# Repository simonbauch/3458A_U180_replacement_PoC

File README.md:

# x180
Second revision of version A PoC functional replacement of the U180 hybrid for the HPAK 3458A A3 ADC.
This time with pulldowns for the control lines and the option to use input fet modulation like on the original U180. Fixed a problem with the input fet modulation.
-- Untested --

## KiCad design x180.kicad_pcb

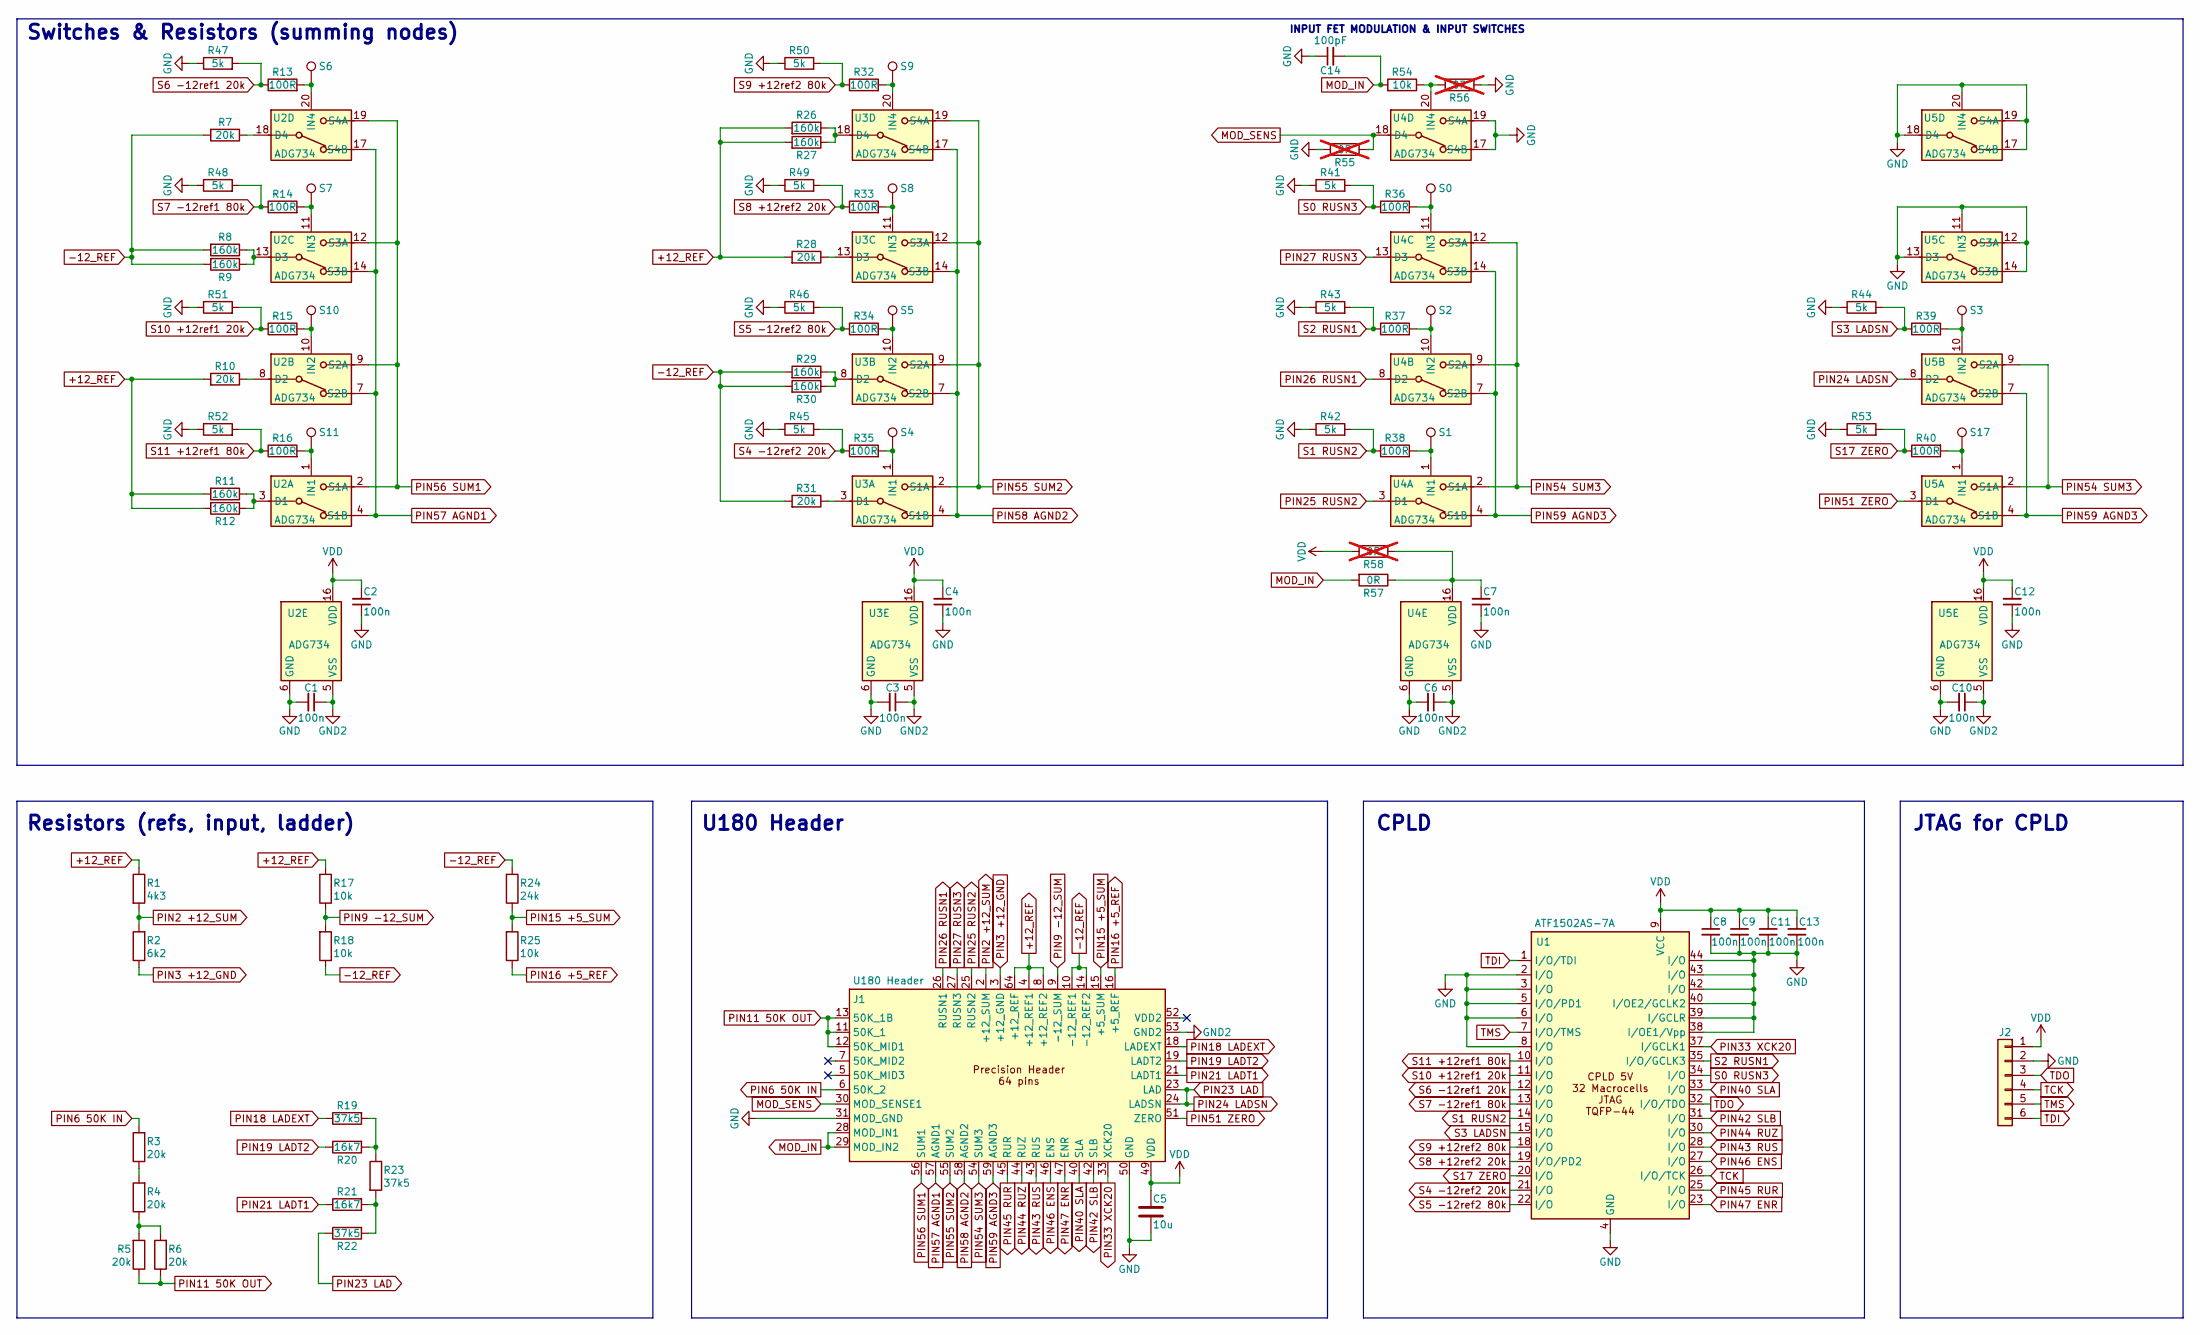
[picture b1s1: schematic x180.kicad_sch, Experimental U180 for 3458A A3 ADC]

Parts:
C1, C2, C3, C4, C6, C7, C8, C9, C10, C11, C12, C13: 100n; C_0603_1608Metric
C5: 10u; C_1206_3216Metric
C14: 100pF; C_0603_1608Metric
J1: U180 Header; U180_HEADER_64P
J2: Conn_01x06_Pin; PinHeader_1x06_P2.54mm_Vertical
R1: 4k3; R_0805_2012Metric
R2: 6k2; R_0805_2012Metric
R3, R4, R5, R6, R7, R10, R28, R31: 20k; R_0805_2012Metric
R8, R9, R11, R12, R26, R27, R29, R30: 160k; R_0805_2012Metric
R13, R14, R15, R16, R32, R33, R34, R35, R36, R37, R38, R39, R40: 100R; R_0603_1608Metric
R17, R18, R25: 10k; R_0805_2012Metric
R19, R22, R23: 37k5; R_0805_2012Metric
R20, R21: 16k7; R_0805_2012Metric
R24: 24k; R_0805_2012Metric
R41, R42, R43, R44, R45, R46, R47, R48, R49, R50, R51, R52, R53: 5k; R_0603_1608Metric
R54: 10k; R_0603_1608Metric
R55, R56, R58: 0R; R_0402_1005Metric; not fitted
R57: 0R; R_0402_1005Metric
S0, S1, S2, S3, S4, S5, S6, S7, S8, S9, S10, S11, S17: TestPoint_Small; TestPoint_Pad_D1.0mm
U1: ATF1502AS-7A; TQFP-44_10x10mm_P0.8mm
U2, U3, U4, U5: ADG734; TSSOP-20_4.4x6.5mm_P0.65mm

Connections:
+12_REF: J1.4 (+12_REF1), J1.8 (+12_REF2), J1.64 (+12_REF), R1.1, R10.2, R11.2, R12.2, R17.2, R26.2, R27.2, R28.2
-12_REF: J1.10 (-12_REF1), J1.14 (-12_REF2), R7.2, R8.2, R9.2, R18.1, R24.2, R29.2, R30.2, R31.2
GND: C1.2, C2.1, C3.2, C4.1, C5.1, C6.2, C7.1, C8.2, C9.2, C10.2, C11.2, C12.1, C13.2, C14.1, J1.20 (GND), J1.22 (GND), J1.31 (MOD_GND), J1.34 (GND), J1.35 (GND), J1.36 (GND), J1.37 (GND), J1.38 (GND), J1.48 (GND), J1.50 (GND), J1.63 (GND), J2.2, R41.1, R42.1, R43.1, R44.1, R45.1, R46.1, R47.1, R48.1, R49.1, R50.1, R51.1, R52.1, R53.1, R55.2, R56.1, U1.2 (I/O), U1.3 (I/O), U1.4 (GND), U1.5 (I/O/PD1), U1.6 (I/O), U1.8 (I/O), U1.16 (GND), U1.24 (GND), U1.36 (GND), U1.38 (I/OE1/Vpp), U1.39 (I/GCLR), U1.40 (I/OE2/GCLK2), U1.42 (I/O), U1.43 (I/O), U1.44 (I/O), U2.6 (GND), U3.6 (GND), U4.6 (GND), U4.17 (S4B), U4.19 (S4A), U5.6 (GND), U5.11 (IN3), U5.12 (S3A), U5.13 (D3), U5.14 (S3B), U5.17 (S4B), U5.18 (D4), U5.19 (S4A), U5.20 (IN4)
GND2: C1.1, C3.1, C6.1, C10.1, J1.53 (GND2), U2.5 (VSS), U3.5 (VSS), U4.5 (VSS), U5.5 (VSS)
MOD_IN: C14.2, J1.28 (MOD_IN1), J1.29 (MOD_IN2), R54.2, R57.2
MOD_SENS: J1.30 (MOD_SENSE1), R55.1, U4.18 (D4)
unnamed: R3.1, R4.2
unnamed: R4.1, R5.2, R6.2
unnamed: R19.2, R20.2, R23.1
unnamed: R21.2, R22.2, R23.2
unnamed: R11.1, R12.1, U2.3 (D1)
unnamed: R16.2, S11.1, U2.1 (IN1)
unnamed: R10.1, U2.8 (D2)
unnamed: R15.2, S10.1, U2.10 (IN2)
unnamed: R8.1, R9.1, U2.13 (D3)
unnamed: R14.2, S7.1, U2.11 (IN3)
unnamed: R7.1, U2.18 (D4)
unnamed: R13.2, S6.1, U2.20 (IN4)
unnamed: R31.1, U3.3 (D1)
unnamed: R35.2, S4.1, U3.1 (IN1)
unnamed: R29.1, R30.1, U3.8 (D2)
unnamed: R34.2, S5.1, U3.10 (IN2)
unnamed: R28.1, U3.13 (D3)
unnamed: R33.2, S8.1, U3.11 (IN3)
unnamed: R26.1, R27.1, U3.18 (D4)
unnamed: R32.2, S9.1, U3.20 (IN4)
unnamed: R38.2, S1.1, U4.1 (IN1)
unnamed: R37.2, S2.1, U4.10 (IN2)
unnamed: R36.2, S0.1, U4.11 (IN3)
unnamed: R54.1, R56.2, U4.20 (IN4)
unnamed: C7.2, R57.1, R58.1, U4.16 (VDD)
unnamed: R40.2, S17.1, U5.1 (IN1)
unnamed: R39.2, S3.1, U5.10 (IN2)
PIN2 +12_SUM: J1.2 (+12_SUM), R1.2, R2.2
PIN3 +12_GND: J1.3 (+12_GND), R2.1
PIN6 50K IN: J1.6 (50K_2), R3.2
PIN9 -12_SUM: J1.9 (-12_SUM), R17.1, R18.2
PIN11 50K OUT: J1.11 (50K_1), J1.12 (50K_MID1), J1.13 (50K_1B), R5.1, R6.1
PIN15 +5_SUM: J1.15 (+5_SUM), R24.1, R25.2
PIN16 +5_REF: J1.16 (+5_REF), R25.1
PIN18 LADEXT: J1.18 (LADEXT), R19.1
PIN19 LADT2: J1.19 (LADT2), R20.1
PIN21 LADT1: J1.21 (LADT1), R21.1
PIN23 LAD: J1.23 (LAD), J1.24 (LADSN), R22.1, U5.8 (D2)
PIN25 RUSN2: J1.25 (RUSN2), U4.3 (D1)
PIN26 RUSN1: J1.26 (RUSN1), U4.8 (D2)
PIN27 RUSN3: J1.27 (RUSN3), U4.13 (D3)
PIN33 XCK20: J1.33 (XCK20), U1.37 (I/GCLK1)
PIN40 SLA: J1.40 (SLA), U1.33 (I/O)
PIN42 SLB: J1.42 (SLB), U1.31 (I/O)
PIN43 RUS: J1.43 (RUS), U1.28 (I/O)
PIN44 RUZ: J1.44 (RUZ), U1.30 (I/O)
PIN45 RUR: J1.45 (RUR), U1.25 (I/O)
PIN46 ENS: J1.46 (ENS), U1.27 (I/O)
PIN47 ENR: J1.47 (ENR), U1.23 (I/O)
PIN51 ZERO: J1.51 (ZERO), U5.3 (D1)
PIN54 SUM3: J1.54 (SUM3), U4.2 (S1A), U4.9 (S2A), U4.12 (S3A), U5.2 (S1A), U5.9 (S2A)
PIN55 SUM2: J1.55 (SUM2), U3.2 (S1A), U3.9 (S2A), U3.12 (S3A), U3.19 (S4A)
PIN56 SUM1: J1.56 (SUM1), U2.2 (S1A), U2.9 (S2A), U2.12 (S3A), U2.19 (S4A)
PIN57 AGND1: J1.57 (AGND1), U2.4 (S1B), U2.7 (S2B), U2.14 (S3B), U2.17 (S4B)
PIN58 AGND2: J1.58 (AGND2), U3.4 (S1B), U3.7 (S2B), U3.14 (S3B), U3.17 (S4B)
PIN59 AGND3: J1.59 (AGND3), U4.4 (S1B), U4.7 (S2B), U4.14 (S3B), U5.4 (S1B), U5.7 (S2B)
S0 RUSN3: R36.1, R41.2, U1.34 (I/O)
S1 RUSN2: R38.1, R42.2, U1.14 (I/O)
S2 RUSN1: R37.1, R43.2, U1.35 (I/O/GCLK3)
S3 LADSN: R39.1, R44.2, U1.15 (I/O)
S4 -12ref2 20k: R35.1, R45.2, U1.21 (I/O)
S5 -12ref2 80k: R34.1, R46.2, U1.22 (I/O)
S6 -12ref1 20k: R13.1, R47.2, U1.12 (I/O)
S7 -12ref1 80k: R14.1, R48.2, U1.13 (I/O)
S8 +12ref2 20k: R33.1, R49.2, U1.19 (I/O/PD2)
S9 +12ref2 80k: R32.1, R50.2, U1.18 (I/O)
S10 +12ref1 20k: R15.1, R51.2, U1.11 (I/O)
S11 +12ref1 80k: R16.1, R52.2, U1.10 (I/O)
S17 ZERO: R40.1, R53.2, U1.20 (I/O)
TCK: J2.4, U1.26 (I/O/TCK)
TDI: J2.6, U1.1 (I/O/TDI)
TDO: J2.3, U1.32 (I/O/TDO)
TMS: J2.5, U1.7 (I/O/TMS)
VDD: C2.2, C4.2, C5.2, C8.1, C9.1, C11.1, C12.2, C13.1, J1.49 (VDD), J2.1, R58.2, U1.9 (VCC), U1.17 (VCC), U1.29 (VCC), U1.41 (VCC), U2.16 (VDD), U3.16 (VDD), U5.16 (VDD)

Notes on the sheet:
INPUT FET MODULATION & INPUT SWITCHES
JTAG for CPLD
Resistors (refs, input, ladder)
Switches & Resistors (summing nodes)
U180 Header
CPLD

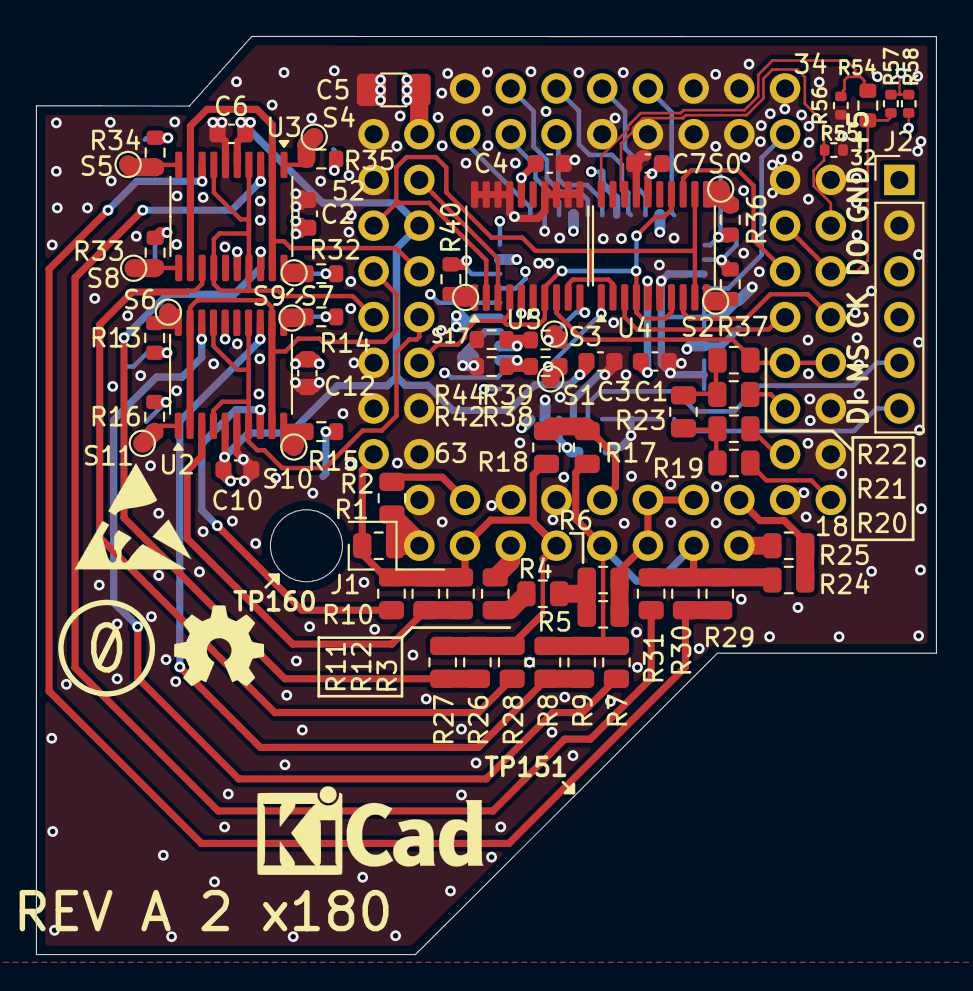
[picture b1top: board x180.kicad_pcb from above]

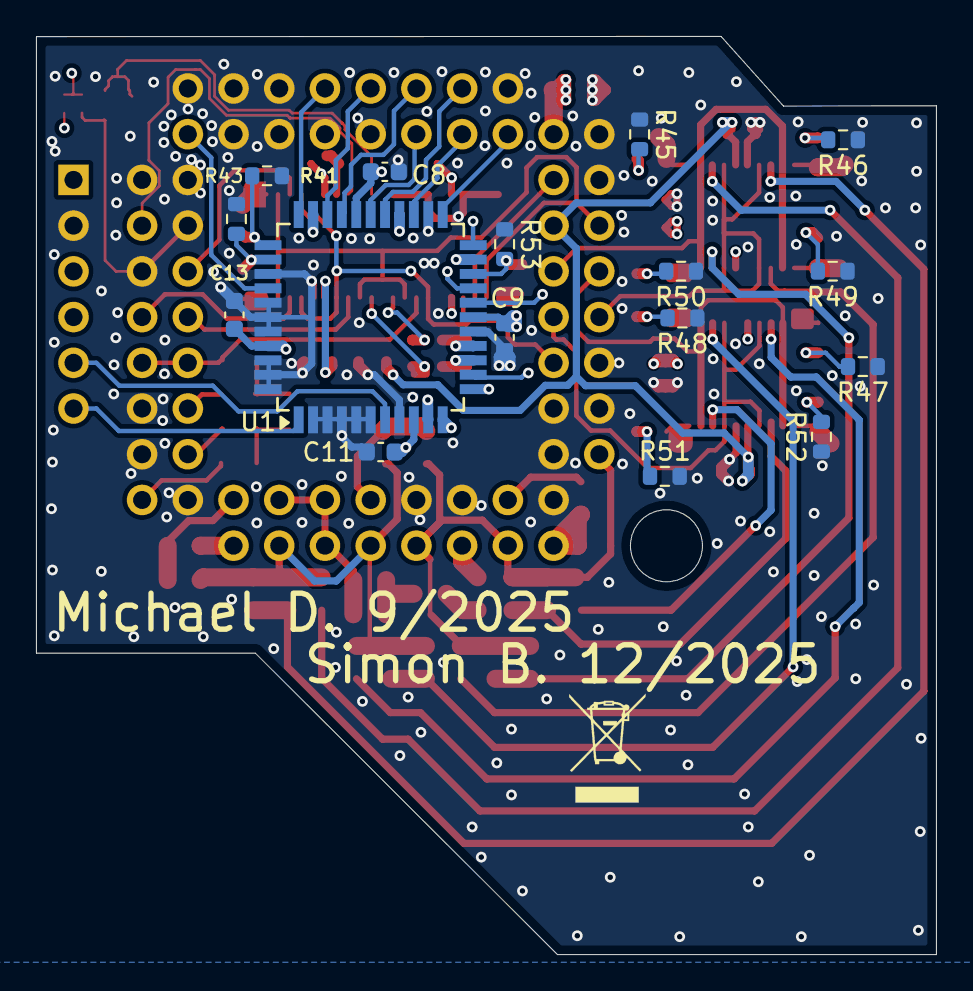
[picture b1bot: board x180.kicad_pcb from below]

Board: 6 copper layers, 50.0 x 51.0 mm, 91 parts (16 on the bottom side), 80 nets.

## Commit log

2025-12-03 Update of PCB
    Update with pulldowns for the control lines and the option to use gate modulation. Also added CPLD code with pinkeep disabled. (Required for linearity, one needs to connect the JTAG lines to GND afte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
2025-12-03 deleted obsoltete files
2026-01-02 Fixed the gate voltage modulation
